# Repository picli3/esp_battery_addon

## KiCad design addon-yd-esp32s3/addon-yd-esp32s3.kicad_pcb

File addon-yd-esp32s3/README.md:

# Addon Battery YD-ESP32-S3

The idea for this module arose from the need to provide autonomy to my **ESP32-S3 modules from the manufacturer VCC-GND**, one of the most popular development kits for the [ESP32](https://s.click.aliexpress.com/e/_c3trfFHh) outside of Espressif itself.

This module provides autonomy to the **YD-ESP32-S3** development board, integrating a rechargeable 18650 battery with charge control, protection, and regulated outputs. It also exposes a 14-pin connector with 5V and 3.3V voltages and some GPIOs for connecting sensors or other peripherals.

|                                 |                                 |
| :-----------------------------: | :-----------------------------: |
|  |  |

---

## Main features

- **Battery**: Rechargeable 18650 cell (Li-Ion).
- **Charging Management**:
  - Integrated **TP4056** for USB charging.
  - Standard charging current (1A max, configurable with resistor).
- **Battery Protection**:
- **DW01A + dual MOSFET** circuit for overcharge, overdischarge, and overcurrent.
- **Power Supplies**:
- **Regulated 5V**: Constant output to power the YD-ESP32-S3 board.
- **Regulated 3.3V** (optional): Available for low-voltage sensors and peripherals.
- **14-pin Expansion Connector**:
- **5V** and **3.3V** outputs.
  - Some exposed **GPIOs** of the ESP32-S3.
  - Common GND.

## 14-pin connector pinout

| Pin | Señal  | Descripción                           |
| --- | ------ | ------------------------------------- |
| 1   | 3.3V   | Salida regulada 3.3V (opcional)       |
| 2   | GND    | GND                                   |
| 3   | GPIO39 | GPIO de la ESP32-S3                   |
| 4   | GPIO40 | GPIO de la ESP32-S3                   |
| 5   | GPIO2  | GPIO de la ESP32-S3                   |
| 6   | GPIO1  | GPIO de la ESP32-S3                   |
| 7   | RXD0   |                                       |
| 8   | TXD0   |                                       |
| 9   | GPIO4  | GPIO de la ESP32-S3                   |
| 10  | GPIO5  | GPIO de la ESP32-S3                   |
| 11  | GPIO8  | GPIO de la ESP32-S3                   |
| 12  | GPIO9  | GPIO de la ESP32-S3                   |
| 13  | GND    | Tierra común                          |
| 14  | 5V     | Salida regulada 5V (para la ESP32-S3) |

*(The exposed GPIOs depend on the assignment you choose in the PCB layout, here they are indicated as placeholders `GPIOx`, `GPIOy`, etc.)*

---

## Considerations

- The module is intended for **standalone use** in projects involving the YD-ESP32-S3.
- The **5V output must always be available**, as it is the primary power source for the ESP32-S3.
- The **3.3V output is optional** and is primarily intended for low-power sensors.
- The protection circuit prevents battery damage, but it is recommended to always use **quality 18650 cells with internal protection**.

## Future improvements

- Support for solar panel charging (MPPT or "solar-friendly" charger).
- Integration of an I²C fuel gauge (e.g., MAX17048) to report battery level.
- General on/off switch.
- Ultra-low-power modes for long-running projects.

## Generate panel

To do this it is required [Kikit](https://github.com/yaqwsx/KiKit?tab=readme-ov-file)

```sh
kikit panelize \
    --layout 'grid; rows: 6; cols: 2; space: 2mm' \
    --tabs 'fixed; width: 3mm; vcount: 2' \
    --cuts 'mousebites; drill: 0.5mm; spacing: 1mm; offset: 0.2mm; prolong: 0.5mm' \
    --framing 'railstb; width: 5mm; space: 3mm;' \
    --tooling '3hole; hoffset: 2.5mm; voffset: 2.5mm; size: 1.5mm' \
    --fiducials '3fid; hoffset: 5mm; voffset: 2.5mm; coppersize: 2mm; opening: 1mm;' \
    --text 'simple; text: MaykolRey.com; anchor: mt; voffset: 2.5mm; hjustify: center; vjustify: center;' \
    --text2 'simple; text: Created on {date}; anchor: mb; voffset: -2.5mm; hjustify: center; vjustify: center;' \
    --post 'millradius: 1mm' \
    addon-yd-esp32s3.kicad_pcb panel/panel.kicad_pcb
```
## Licence

Author: Maykol Rey

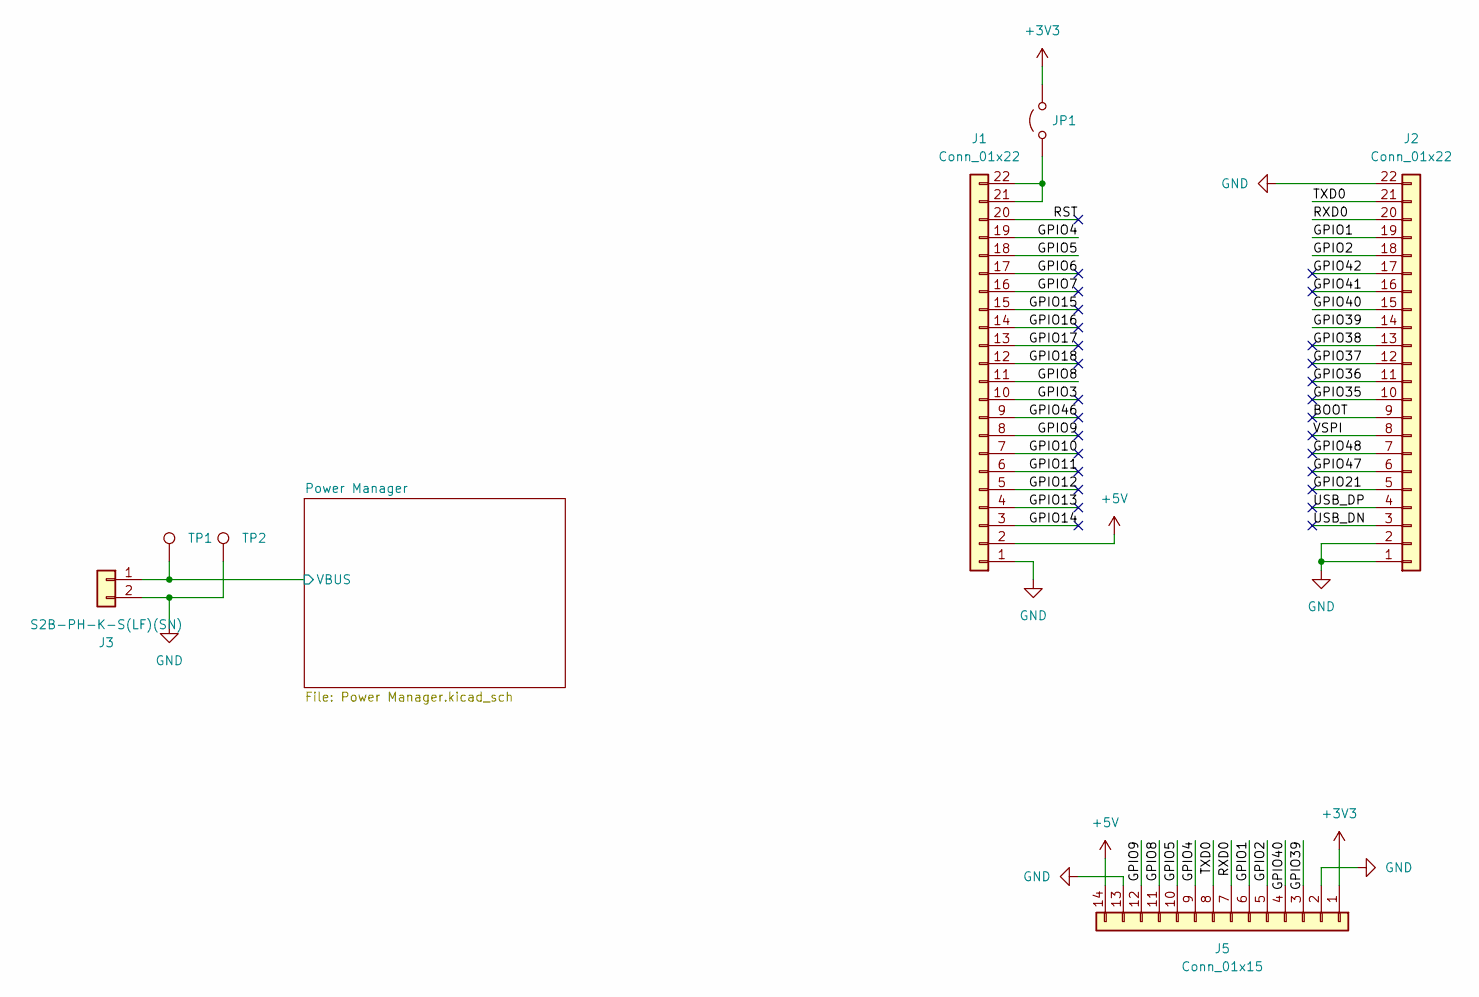
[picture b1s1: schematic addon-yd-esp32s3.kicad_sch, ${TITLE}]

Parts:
J1, J2: Conn_01x22; PinHeader_1x22_P2.54mm_Vertical
J3: S2B-PH-K-S(LF)(SN); JST_PH_S2B-PH-K_1x02_P2.00mm_Horizontal; Part # S2B-PH-K-S(LF)(SN); LCSC C173752
J5: Conn_01x15; PinHeader_1x14_P2.00mm_Vertical
JP1: Jumper_2_Open; SolderJumper-2_P1.3mm_Open_TrianglePad1.0x1.5mm
TP1, TP2: TestPoint; TestPoint_Pad_1.5x1.5mm

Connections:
+3V3: J5.1, JP1.2 (B); also elsewhere on the board
+5V: J1.2, J5.14; also elsewhere on the board
/BOOT: J2.9
/GPIO1: J2.19, J5.6
/GPIO2: J2.18, J5.5
/GPIO3: J1.10
/GPIO4: J1.19, J5.9
/GPIO5: J1.18, J5.10
/GPIO6: J1.17
/GPIO7: J1.16
/GPIO8: J1.11, J5.11
/GPIO9: J1.8, J5.12
/GPIO10: J1.7
/GPIO11: J1.6
/GPIO12: J1.5
/GPIO13: J1.4
/GPIO14: J1.3
/GPIO15: J1.15
/GPIO16: J1.14
/GPIO17: J1.13
/GPIO18: J1.12
/GPIO21: J2.5
/GPIO35: J2.10
/GPIO36: J2.11
/GPIO37: J2.12
/GPIO38: J2.13
/GPIO39: J2.14, J5.3
/GPIO40: J2.15, J5.4
/GPIO41: J2.16
/GPIO42: J2.17
/GPIO46: J1.9
/GPIO47: J2.6
/GPIO48: J2.7
/Power Manager/VBUS: J3.1, TP1.1; also elsewhere on the board
/RST: J1.20
/RXD0: J2.20, J5.7
/TXD0: J2.21, J5.8
/USB_DN: J2.3
/USB_DP: J2.4
/VSPI: J2.8
GND: J1.1, J2.1, J2.2, J2.22, J3.2, J5.2, J5.13, TP2.1; also elsewhere on the board
unnamed: J1.21, J1.22, JP1.1 (A)

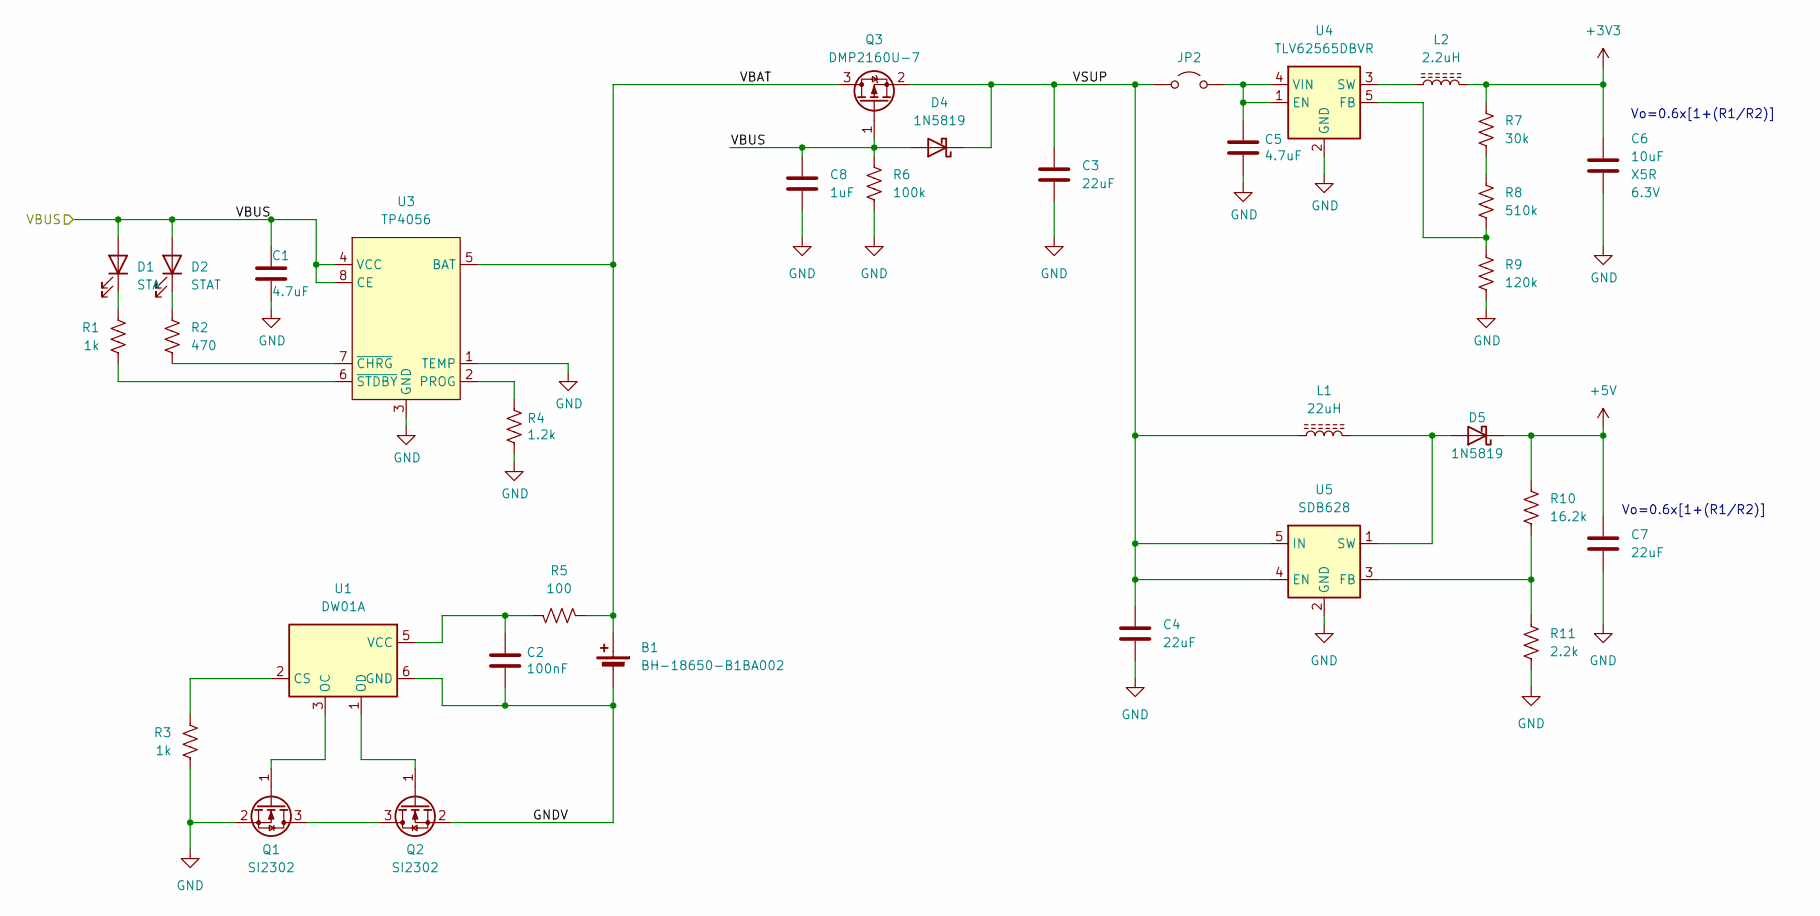
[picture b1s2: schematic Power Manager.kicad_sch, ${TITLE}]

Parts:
B1: BH-18650-B1BA002; BatteryHolder_MYOUNG_B1BA002_1x18650; Part # BH-18650-B1BA002; LCSC C2988620
C1, C5: 4.7uF; C_0603_1608Metric_Pad1.08x0.95mm_HandSolder; Part # CL10A475KP8NNNC; LCSC C1705
C2: 100nF; C_0603_1608Metric_Pad1.08x0.95mm_HandSolder; Part # CL10B104KO8NNNC; LCSC C66501
C3, C4, C7: 22uF; C_0805_2012Metric_Pad1.18x1.45mm_HandSolder; Part # CL21A226MQQNNNE; LCSC C5674
C6: 10uF; C_0805_2012Metric_Pad1.18x1.45mm_HandSolder; Part # CL21A106KPFNNNE; LCSC C17024
C8: 1uF; C_0805_2012Metric; Part # CL21B105KBFNNNE; LCSC C28323
D1: STA; LED_0603_1608Metric_Pad1.05x0.95mm_HandSolder; Part # XL-1608UGC-04; LCSC C965804
D2: STAT; LED_0603_1608Metric_Pad1.05x0.95mm_HandSolder; Part # NCD0603R1; LCSC C84263
D4, D5: 1N5819; D_SOD-123; Part # 1N5819HW-7-F; LCSC C82544
JP2: Jumper_2_Open; SolderJumper-2_P1.3mm_Open_TrianglePad1.0x1.5mm
L1: 22uH; L_Coilcraft_XxL4030; Part # SWPA4030S220MT; LCSC C83472
L2: 2.2uH; L_Taiyo-Yuden_MD-4040; Part # LQH44PN2R2MP0L; LCSC C86081
Q1, Q2: SI2302; SOT-23; Part # SI2302; LCSC C2891732
Q3: DMP2160U-7; SOT-23; Part # DMP2160U-7; LCSC C260875
R1, R3: 1k; R_0603_1608Metric_Pad0.98x0.95mm_HandSolder; Part # 0603WAF1001T5E; LCSC C21190
R2: 470; R_0603_1608Metric_Pad0.98x0.95mm_HandSolder; Part # 0603WAF4700T5E; LCSC C23179
R4: 1.2k; R_0603_1608Metric_Pad0.98x0.95mm_HandSolder; Part # 0603WAF1201T5E; LCSC C22765
R5: 100; R_0603_1608Metric; Part # RC0603FR-07100RL; LCSC C105588
R6: 100k; R_0603_1608Metric; Part # RC0603FR-07100KL; LCSC C14675
R7: 30k; R_0603_1608Metric_Pad0.98x0.95mm_HandSolder; Part # 0603WAF3002T5E; LCSC C22984
R8: 510k; R_0603_1608Metric_Pad0.98x0.95mm_HandSolder; Part # 0603WAF5103T5E; LCSC C23192
R9: 120k; R_0603_1608Metric_Pad0.98x0.95mm_HandSolder; Part # 0603WAF1203T5E; LCSC C25808
R10: 16.2k; R_0603_1608Metric_Pad0.98x0.95mm_HandSolder; Part # 0603WAF1622T5E; LCSC C22885
R11: 2.2k; R_0603_1608Metric_Pad0.98x0.95mm_HandSolder; Part # 0603WAF2201T5E; LCSC C4190
U1: DW01A; SOT-23-6; Part # DW01A; LCSC C351410
U3: TP4056; SOP-8_3.76x4.96mm_P1.27mm; Part # TP4056; LCSC C725790
U4: TLV62565DBVR; SOT-23-5; Part # TLV62565DBVR; LCSC C87122
U5: SDB628; SOT-23-6; Part # SDB628; LCSC C77805

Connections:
+3V3: C6.1, L2.2, R7.1; also elsewhere on the board
+5V: C7.1, D5.1 (K), R10.1; also elsewhere on the board
/Power Manager/GNDV: B1.2 (-), C2.2, Q2.2 (S), U1.6 (GND)
/Power Manager/VBAT: B1.1 (+), Q3.3 (D), R5.1, U3.5 (BAT)
/Power Manager/VBUS: C1.1, C8.1, D1.2 (A), D2.2 (A), D4.2 (A), Q3.1 (G), R6.2, U3.4 (VCC), U3.8 (CE); also elsewhere on the board
/Power Manager/VSUP: C3.1, C4.1, D4.1 (K), JP2.1 (A), L1.1, Q3.2 (S), U5.4 (EN), U5.5 (IN)
GND: C1.2, C3.2, C4.2, C5.2, C6.2, C7.2, C8.2, Q1.2 (S), R3.1, R4.1, R6.1, R9.2, R11.2, U3.1 (TEMP), U3.3 (GND), U4.2 (GND), U5.2 (GND); also elsewhere on the board
unnamed: D1.1 (K), R1.2
unnamed: D2.1 (K), R2.2
unnamed: D5.2 (A), L1.2, U5.1 (SW)
unnamed: C5.1, JP2.2 (B), U4.1 (EN), U4.4 (VIN)
unnamed: Q1.3 (D), Q2.3 (D)
unnamed: Q1.1 (G), U1.3 (OC)
unnamed: Q2.1 (G), U1.1 (OD)
unnamed: R7.2, R8.1
unnamed: R3.2, U1.2 (CS)
unnamed: C2.1, R5.2, U1.5 (VCC)
unnamed: R4.2, U3.2 (PROG)
unnamed: R2.1, U3.7 (~CHRG)
unnamed: R1.1, U3.6 (~STDBY)
unnamed: R8.2, R9.1, U4.5 (FB)
unnamed: L2.1, U4.3 (SW)
unnamed: R10.2, R11.1, U5.3 (FB)

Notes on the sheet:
Vo=0.6x[1+(R1/R2)]

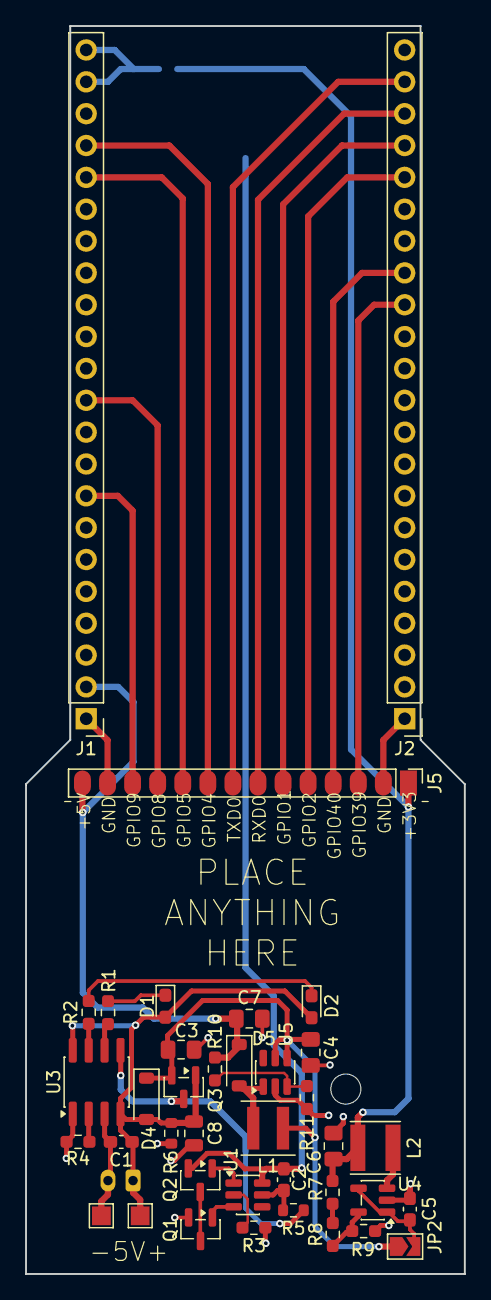
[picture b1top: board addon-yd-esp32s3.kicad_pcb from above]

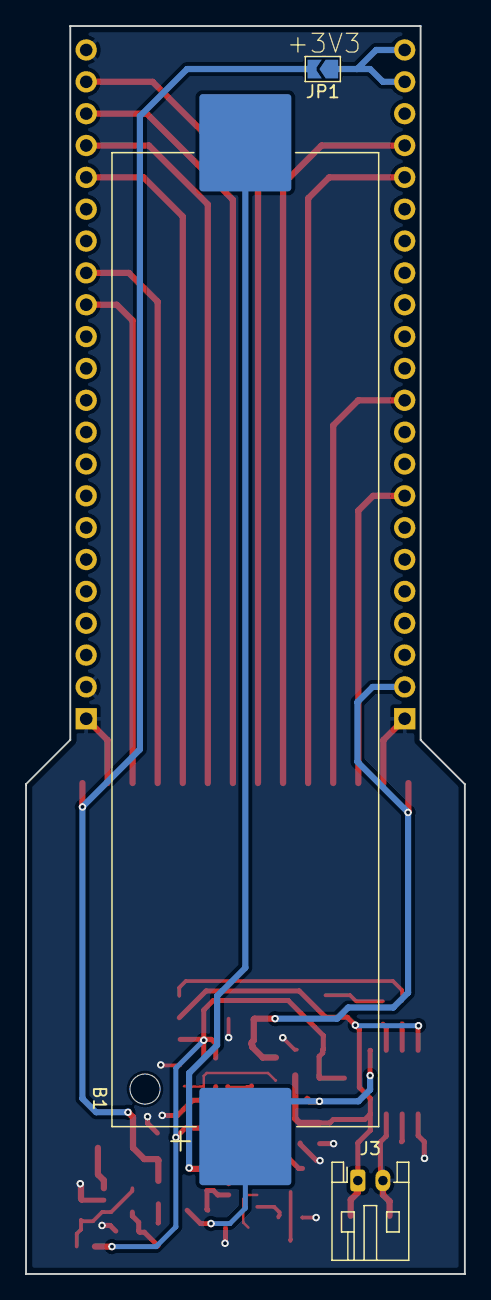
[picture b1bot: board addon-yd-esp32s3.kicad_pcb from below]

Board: 2 copper layers, 35.0 x 99.5 mm, 41 parts (3 on the bottom side), 34 nets.

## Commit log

2025-09-26 primer commit
2025-09-27 completando el diseño
2025-09-29 completando diseño PCB
2025-09-30 completando version 1
2025-09-30 add documentation
2025-09-30 add images
2025-10-01 cambiando el tamaño a 100 mm
2025-10-01 agregando imagenes
